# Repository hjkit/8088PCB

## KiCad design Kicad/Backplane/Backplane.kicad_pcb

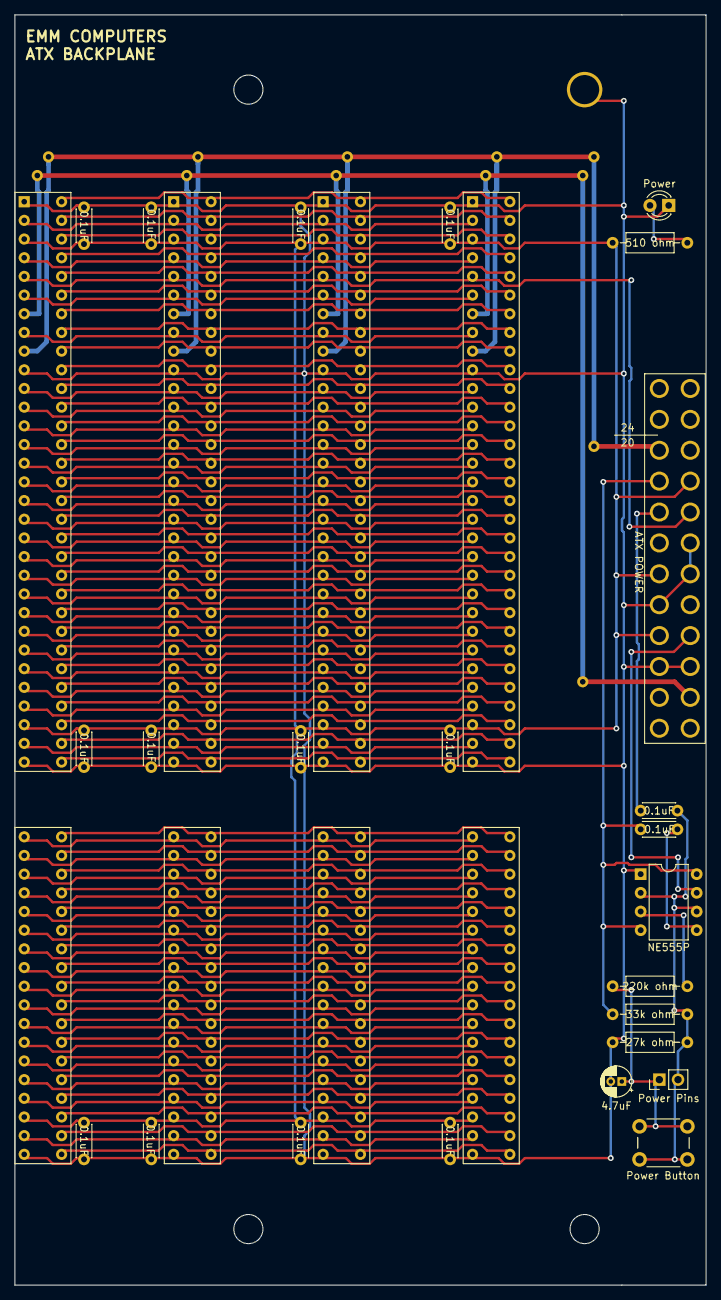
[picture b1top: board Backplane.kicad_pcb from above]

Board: 2 copper layers, 94.0 x 172.7 mm, 40 parts (0 on the bottom side), 101 nets.

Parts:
ATXPOWER1: ATX POWER; 24_PIN_ATX_POWER
C1, C2, C3, C4, C5, C6, C7, C8, C9, C10, C11, C12, C14, C15: 0.1uF; C_Disc_D4.3mm_W1.9mm_P5.00mm
C13: 4.7uF; CP_Radial_D4.0mm_P1.50mm
D1: Power; LED_D3.0mm
ISA1, ISA2, ISA3, ISA4: Bus_ISA_16bit; 16-bit-ISA
J8: Power Pins; PinHeader_1x02_P2.54mm_Vertical
R: L; Large_Via
R1: 27k ohm; R_Axial_DIN0207_L6.3mm_D2.5mm_P10.16mm_Horizontal
R2: 33k ohm; R_Axial_DIN0207_L6.3mm_D2.5mm_P10.16mm_Horizontal
R3: 220k ohm; R_Axial_DIN0207_L6.3mm_D2.5mm_P10.16mm_Horizontal
R4: 510 ohm; R_Axial_DIN0207_L6.3mm_D2.5mm_P10.16mm_Horizontal
R#2, R#3, R#4, R#5, R#6, R#7, R#8, R#9, R#10, R#11, R#12: L; Large_Via
SW1: Power Button; SW_PUSH_6mm
U1: NE555P; DIP-8_W7.62mm

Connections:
/5+: ATXPOWER1.4, ATXPOWER1.6, ATXPOWER1.21, C1.2, C2.2, C3.2, C4.2, C5.2, C6.2, C7.2, C8.2, C9.2, C10.2, C11.2, C12.2, ISA1.3, ISA1.29, ISA1.78, ISA2.3, ISA2.29, ISA2.78, ISA3.3, ISA3.29, ISA3.78, ISA4.3, ISA4.29, ISA4.78, R4.1
/5+SB: ATXPOWER1.9, C14.2, R2.1, U1.4, U1.8
/5-: ATXPOWER1.20, ISA1.5, ISA2.5, ISA3.5, ISA4.5
/12+: ATXPOWER1.10, ISA1.9, ISA2.9, ISA3.9, ISA4.9, R.1, R#3.1, R#5.1, R#6.1, R#8.1, R#12.1
/12-: ATXPOWER1.14, ISA1.7, ISA2.7, ISA3.7, ISA4.7, R#2.1, R#4.1, R#7.1, R#9.1, R#10.1, R#11.1
/A0: ISA1.62, ISA2.62, ISA3.62, ISA4.62
/A1: ISA1.61, ISA2.61, ISA3.61, ISA4.61
/A2: ISA1.60, ISA2.60, ISA3.60, ISA4.60
/A3: ISA1.59, ISA2.59, ISA3.59, ISA4.59
/A4: ISA1.58, ISA2.58, ISA3.58, ISA4.58
/A5: ISA1.57, ISA2.57, ISA3.57, ISA4.57
/A6: ISA1.56, ISA2.56, ISA3.56, ISA4.56
/A7: ISA1.55, ISA2.55, ISA3.55, ISA4.55
/A8: ISA1.54, ISA2.54, ISA3.54, ISA4.54
/A9: ISA1.53, ISA2.53, ISA3.53, ISA4.53
/A10: ISA1.52, ISA2.52, ISA3.52, ISA4.52
/A11: ISA1.51, ISA2.51, ISA3.51, ISA4.51
/A12: ISA1.50, ISA2.50, ISA3.50, ISA4.50
/A13: ISA1.49, ISA2.49, ISA3.49, ISA4.49
/A14: ISA1.48, ISA2.48, ISA3.48, ISA4.48
/A15: ISA1.47, ISA2.47, ISA3.47, ISA4.47
/A16: ISA1.46, ISA2.46, ISA3.46, ISA4.46
/A17: ISA1.45, ISA2.45, ISA3.45, ISA4.45
/A18: ISA1.44, ISA2.44, ISA3.44, ISA4.44
/A19: ISA1.43, ISA2.43, ISA3.43, ISA4.43
/AEN: ISA1.42, ISA2.42, ISA3.42, ISA4.42
/ALE: ISA1.28, ISA2.28, ISA3.28, ISA4.28
/BUTTON_INPUT: C13.1, J8.1, R3.1, SW1.1
/BUTTON_OUTPUT: C15.2, J8.2, R1.2, R2.2, SW1.2, U1.2, U1.6
/CLK: ISA1.20, ISA2.20, ISA3.20, ISA4.20
/CVOLT: C14.1, U1.5
/D0: ISA1.40, ISA2.40, ISA3.40, ISA4.40
/D1: ISA1.39, ISA2.39, ISA3.39, ISA4.39
/D2: ISA1.38, ISA2.38, ISA3.38, ISA4.38
/D3: ISA1.37, ISA2.37, ISA3.37, ISA4.37
/D4: ISA1.36, ISA2.36, ISA3.36, ISA4.36
/D5: ISA1.35, ISA2.35, ISA3.35, ISA4.35
/D6: ISA1.34, ISA2.34, ISA3.34, ISA4.34
/D7: ISA1.33, ISA2.33, ISA3.33, ISA4.33
/D8: ISA1.91, ISA2.91, ISA3.91, ISA4.91
/D9: ISA1.92, ISA2.92, ISA3.92, ISA4.92
/D10: ISA1.93, ISA2.93, ISA3.93, ISA4.93
/D11: ISA1.94, ISA2.94, ISA3.94, ISA4.94
/D12: ISA1.95, ISA2.95, ISA3.95, ISA4.95
/D13: ISA1.96, ISA2.96, ISA3.96, ISA4.96
/D14: ISA1.97, ISA2.97, ISA3.97, ISA4.97
/D15: ISA1.98, ISA2.98, ISA3.98, ISA4.98
/DACK0: ISA1.70, ISA2.70, ISA3.70, ISA4.70
/DACK1: ISA1.17, ISA2.17, ISA3.17, ISA4.17
/DACK2: ISA1.26, ISA2.26, ISA3.26, ISA4.26
/DACK3: ISA1.15, ISA2.15, ISA3.15, ISA4.15
/DACK5: ISA1.72, ISA2.72, ISA3.72, ISA4.72
/DACK6: ISA1.74, ISA2.74, ISA3.74, ISA4.74
/DACK7: ISA1.76, ISA2.76, ISA3.76, ISA4.76
/DRQ0: ISA1.71, ISA2.71, ISA3.71, ISA4.71
/DRQ1: ISA1.18, ISA2.18, ISA3.18, ISA4.18
/DRQ2: ISA1.6, ISA2.6, ISA3.6, ISA4.6
/DRQ3: ISA1.16, ISA2.16, ISA3.16, ISA4.16
/DRQ5: ISA1.73, ISA2.73, ISA3.73, ISA4.73
/DRQ6: ISA1.75, ISA2.75, ISA3.75, ISA4.75
/DRQ7: ISA1.77, ISA2.77, ISA3.77, ISA4.77
/GND: ATXPOWER1.3, ATXPOWER1.5, ATXPOWER1.15, ATXPOWER1.18, ATXPOWER1.19, C1.1, C2.1, C3.1, C4.1, C5.1, C6.1, C7.1, C8.1, C9.1, C10.1, C11.1, C12.1, C13.2, D1.1, ISA1.1, ISA1.10, ISA1.31, ISA1.80, ISA2.1, ISA2.10, ISA2.31, ISA2.80, ISA3.1, ISA3.10, ISA3.31, ISA3.80, ISA4.1, ISA4.10, ISA4.31, ISA4.80, R1.1, U1.1
/IO: ISA1.32, ISA2.32, ISA3.32, ISA4.32
/IOCS16: ISA1.64, ISA2.64, ISA3.64, ISA4.64
/IOR: ISA1.14, ISA2.14, ISA3.14, ISA4.14
/IOW: ISA1.13, ISA2.13, ISA3.13, ISA4.13
/IO_READY: ISA1.41, ISA2.41, ISA3.41, ISA4.41
/IRQ2: ISA1.4, ISA2.4, ISA3.4, ISA4.4
/IRQ3: ISA1.25, ISA2.25, ISA3.25, ISA4.25
/IRQ4: ISA1.24, ISA2.24, ISA3.24, ISA4.24
/IRQ5: ISA1.23, ISA2.23, ISA3.23, ISA4.23
/IRQ6: ISA1.22, ISA2.22, ISA3.22, ISA4.22
/IRQ7: ISA1.21, ISA2.21, ISA3.21, ISA4.21
/IRQ10: ISA1.65, ISA2.65, ISA3.65, ISA4.65
/IRQ11: ISA1.66, ISA2.66, ISA3.66, ISA4.66
/IRQ12: ISA1.67, ISA2.67, ISA3.67, ISA4.67
/IRQ14: ISA1.69, ISA2.69, ISA3.69, ISA4.69
/IRQ15: ISA1.68, ISA2.68, ISA3.68, ISA4.68
/LA17: ISA1.88, ISA2.88, ISA3.88, ISA4.88
/LA18: ISA1.87, ISA2.87, ISA3.87, ISA4.87
/LA19: ISA1.86, ISA2.86, ISA3.86, ISA4.86
/LA20: ISA1.85, ISA2.85, ISA3.85, ISA4.85
/LA21: ISA1.84, ISA2.84, ISA3.84, ISA4.84
/LA22: ISA1.83, ISA2.83, ISA3.83, ISA4.83
/LA23: ISA1.82, ISA2.82, ISA3.82, ISA4.82
/LEDR: D1.2, R4.2
/MASTER: ISA1.79, ISA2.79, ISA3.79, ISA4.79
/MEMCS16: ISA1.63, ISA2.63, ISA3.63, ISA4.63
/MEMR: ISA1.89, ISA2.89, ISA3.89, ISA4.89
/MEMW: ISA1.90, ISA2.90, ISA3.90, ISA4.90
/NC: ISA1.8, ISA2.8, ISA3.8, ISA4.8
/OSC: ISA1.30, ISA2.30, ISA3.30, ISA4.30
/OUT: R3.2, U1.3
/POWER_GOOD: ATXPOWER1.8, C15.1
/POWER_ON: ATXPOWER1.16, U1.7
/REF: ISA1.19, ISA2.19, ISA3.19, ISA4.19
/RESET: ISA1.2, ISA2.2, ISA3.2, ISA4.2
/SBHE: ISA1.81, ISA2.81, ISA3.81, ISA4.81
/SMEMR: ISA1.12, ISA2.12, ISA3.12, ISA4.12
/SMEMW: ISA1.11, ISA2.11, ISA3.11, ISA4.11
/TC: ISA1.27, ISA2.27, ISA3.27, ISA4.27

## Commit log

2025-02-24 Added ATX backplane
    added
